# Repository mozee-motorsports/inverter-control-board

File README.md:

# mp7_ied (isolation-expansion-device)

Isolated CAN-addressable analog throttle for Sevcon.

- firmware in `src/`
  - to build: install Raspberry Pi Pico extension in vscode, open folder, click compile on bottom bar. 
- kicad project in `pcb/`

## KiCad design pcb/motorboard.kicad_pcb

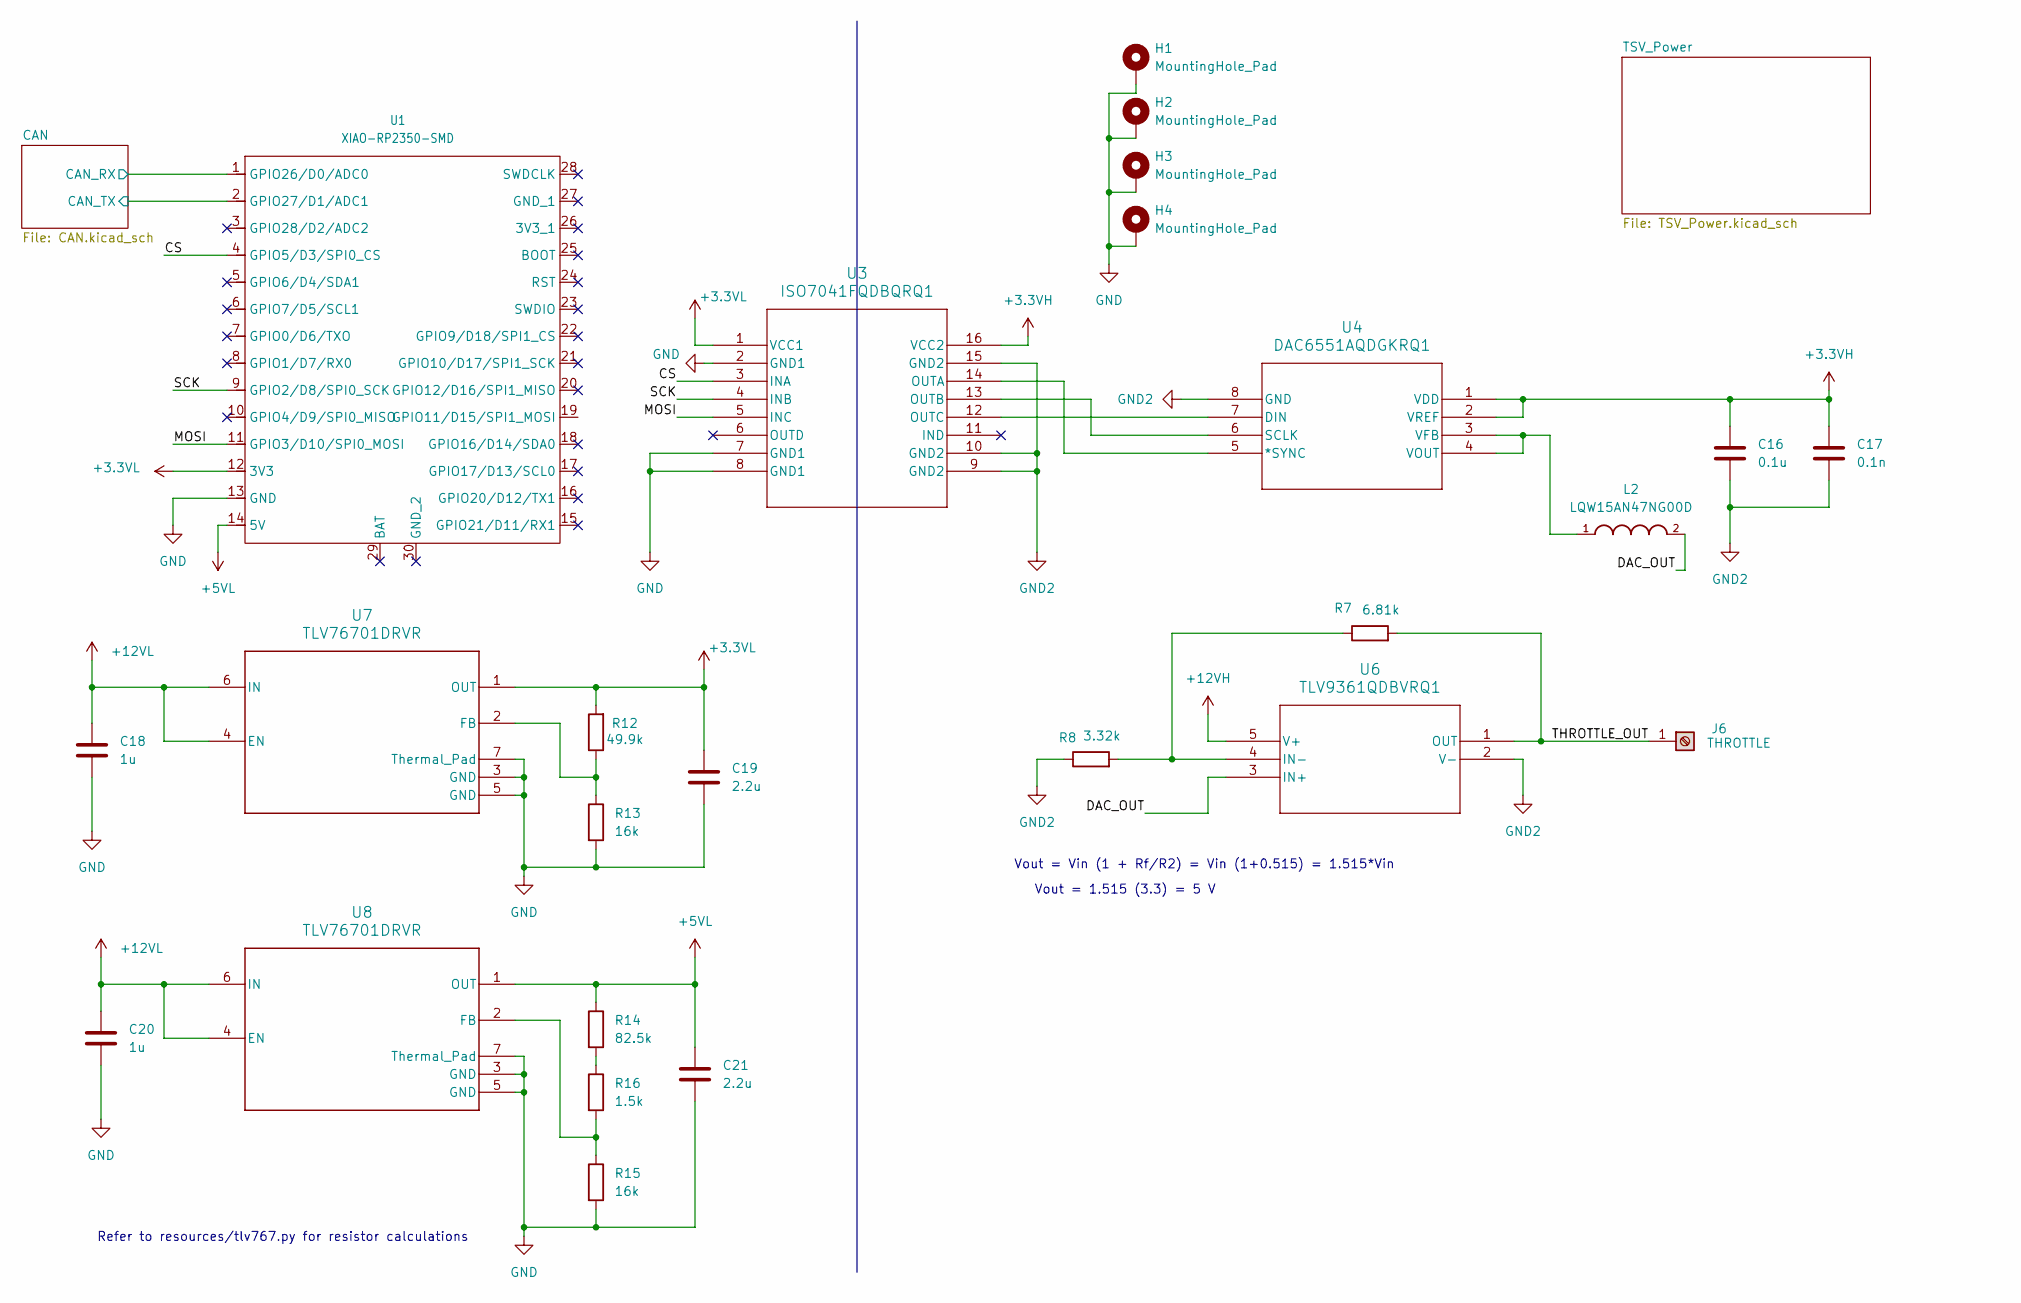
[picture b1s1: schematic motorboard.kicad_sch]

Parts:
C16: 0.1u; C_0603_1608Metric
C17: 0.1n; C_0603_1608Metric
C18, C20: 1u; C_0603_1608Metric
C19, C21: 2.2u; C_0603_1608Metric
H1, H2, H3, H4: MountingHole_Pad; MountingHole_2.2mm_M2
J6: THROTTLE; Wuerth_REDCUBE-THR_WP-THRBU_74650074_THR
L2: LQW15AN47NG00D; INDC1005X60N
R7: 6.81k; R_0603_1608Metric
R8: 3.32k; R_0603_1608Metric
R12: 49.9k; R_0603_1608Metric
R13, R15: 16k; R_0603_1608Metric
R14: 82.5k; R_0603_1608Metric
R16: 1.5k; R_0603_1608Metric
U1: XIAO-RP2350-SMD
U3: ISO7041FQDBQRQ1; SSOP16_DBQ_TEX
U4: DAC6551AQDGKRQ1; DGK8_TEX
U6: TLV9361QDBVRQ1; SOT23_DBV_TEX
U7, U8: TLV76701DRVR; DRV0006A-IPC_A

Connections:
+3.3VH: C16.1, C17.1, U3.16 (VCC2), U4.1 (VDD), U4.2 (VREF); also elsewhere on the board
+3.3VL: C19.1, R12.2, U1.12 (3V3), U3.1 (VCC1), U7.1 (OUT); also elsewhere on the board
+5VL: C21.1, R14.1, U1.14 (5V), U8.1 (OUT); also elsewhere on the board
+12VH: U6.5 (V+); also elsewhere on the board
+12VL: C18.1, C20.1, U7.4 (EN), U7.6 (IN), U8.4 (EN), U8.6 (IN); also elsewhere on the board
/CAN/CAN_RX: U1.1 (GPIO26/D0/ADC0); also elsewhere on the board
/CAN/CAN_TX: U1.2 (GPIO27/D1/ADC1); also elsewhere on the board
/CS: U1.4 (GPIO5/D3/SPI0_CS), U3.3 (INA)
/DAC_OUT: L2.2, U6.3 (IN+)
/MOSI: U1.11 (GPIO3/D10/SPI0_MOSI), U3.5 (INC)
/SCK: U1.9 (GPIO2/D8/SPI0_SCK), U3.4 (INB)
/THROTTLE_OUT: J6.1, R7.2, U6.1 (OUT)
GND: C18.2, C19.2, C20.2, C21.2, H1.1, H2.1, H3.1, H4.1, R13.2, R15.2, U1.13 (GND), U3.2 (GND1), U3.7 (GND1), U3.8 (GND1), U7.3 (GND), U7.5 (GND), U7.7 (Thermal_Pad), U8.3 (GND), U8.5 (GND), U8.7 (Thermal_Pad); also elsewhere on the board
GND2: C16.2, C17.2, R8.1, U3.9 (GND2), U3.10 (GND2), U3.15 (GND2), U4.8 (GND), U6.2 (V-); also elsewhere on the board
unnamed: R14.2, R16.1
unnamed: U3.14 (OUTA), U4.5 (*SYNC)
unnamed: U3.13 (OUTB), U4.6 (SCLK)
unnamed: U3.12 (OUTC), U4.7 (DIN)
unnamed: L2.1, U4.3 (VFB), U4.4 (VOUT)
unnamed: R7.1, R8.2, U6.4 (IN-)
unnamed: R12.1, R13.1, U7.2 (FB)
unnamed: R15.1, R16.2, U8.2 (FB)

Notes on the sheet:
Vout = 1.515 (3.3) = 5 V
Refer to resources/tlv767.py for resistor calculations
Vout = Vin (1 + Rf/R2) = Vin (1+0.515) = 1.515*Vin

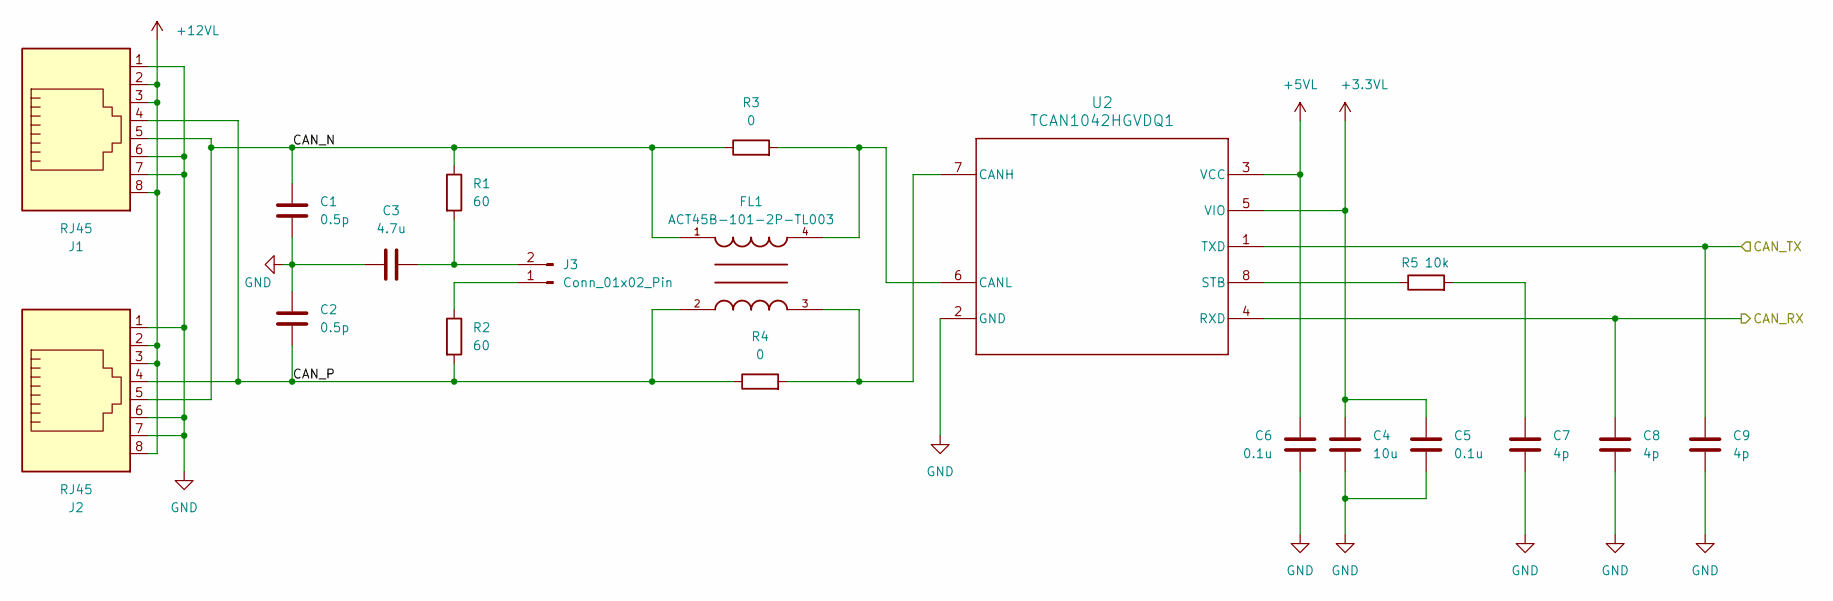
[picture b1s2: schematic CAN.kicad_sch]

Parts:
C1, C2: 0.5p; C_0402_1005Metric
C3: 4.7u; C_0805_2012Metric
C4: 10u; C_0805_2012Metric
C5, C6: 0.1u; C_0603_1608Metric
C7, C8, C9: 4p; C_0603_1608Metric
FL1: ACT45B-101-2P-TL003; FIL_ACT45B-101-2P-TL003; PARTREV 20200405
J1, J2: RJ45; RJ45_Amphenol_54602-x08_Horizontal
J3: Conn_01x02_Pin; PinHeader_1x02_P2.54mm_Vertical
R1, R2: 60; R_0603_1608Metric
R3, R4: 0; R_0603_1608Metric
R5: 10k; R_0603_1608Metric
U2: TCAN1042HGVDQ1; D0008A_L

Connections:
+3.3VL: C4.1, C5.1, U2.5 (VIO); also elsewhere on the board
+5VL: C6.2, U2.3 (VCC); also elsewhere on the board
+12VL: J1.2, J1.3, J1.8, J2.2, J2.3, J2.8; also elsewhere on the board
/CAN/CAN_N: C1.2, FL1.1, J1.5, J2.5, R1.1, R3.1
/CAN/CAN_P: C2.1, FL1.2, J1.4, J2.4, R2.2, R4.1
/CAN/CAN_RX: C8.1, U2.4 (RXD); also elsewhere on the board
/CAN/CAN_TX: C9.1, U2.1 (TXD); also elsewhere on the board
GND: C1.1, C2.2, C3.2, C4.2, C5.2, C6.1, C7.2, C8.2, C9.2, J1.1, J1.6, J1.7, J2.1, J2.6, J2.7, U2.2 (GND); also elsewhere on the board
unnamed: C7.1, R5.2
unnamed: J3.1, R2.1
unnamed: C3.1, J3.2, R1.2
unnamed: FL1.3, R4.2, U2.7 (CANH)
unnamed: FL1.4, R3.2, U2.6 (CANL)
unnamed: R5.1, U2.8 (STB)

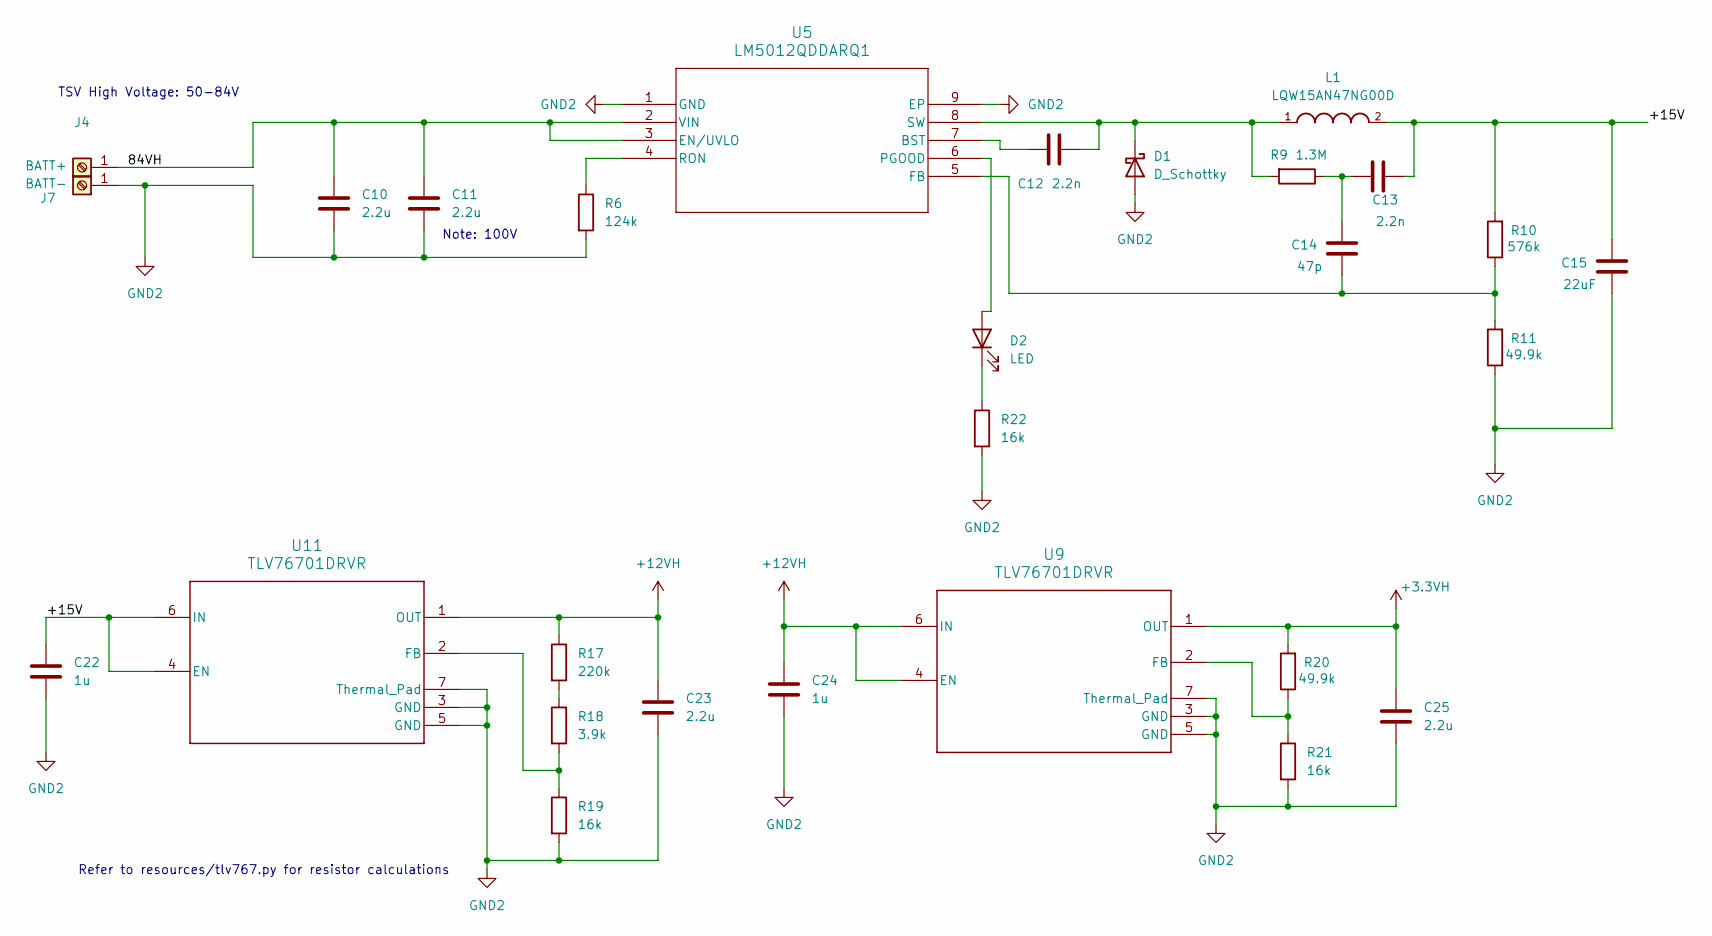
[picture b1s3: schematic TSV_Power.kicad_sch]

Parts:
C10, C11: 2.2u; C_1210_3225Metric_Pad1.33x2.70mm_HandSolder
C12, C13: 2.2n; C_0805_2012Metric
C14: 47p; C_0805_2012Metric
C15: 22uF; C_1210_3225Metric
C22, C24: 1u; C_0603_1608Metric
C23, C25: 2.2u; C_0603_1608Metric
D1: D_Schottky; D_DO-201AD_P15.24mm_Horizontal
D2: LED; LED_0805_2012Metric
J4: BATT+; Wuerth_REDCUBE-THR_WP-THRBU_74650074_THR
J7: BATT-; Wuerth_REDCUBE-THR_WP-THRBU_74650074_THR
L1: LQW15AN47NG00D; INDC1005X60N
R6: 124k; R_0402_1005Metric
R9: 1.3M; R_0402_1005Metric_Pad0.72x0.64mm_HandSolder
R10: 576k; R_0603_1608Metric
R11, R20: 49.9k; R_0603_1608Metric
R17: 220k; R_0603_1608Metric
R18: 3.9k; R_0603_1608Metric
R19, R21, R22: 16k; R_0603_1608Metric
U5: LM5012QDDARQ1; SO-8-DDA_TEX
U9, U11: TLV76701DRVR; DRV0006A-IPC_A

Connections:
+3.3VH: C25.1, R20.2, U9.1 (OUT); also elsewhere on the board
+12VH: C23.1, C24.1, R17.1, U9.4 (EN), U9.6 (IN), U11.1 (OUT); also elsewhere on the board
/TSV_Power/84VH: C10.1, C11.1, J4.1, U5.2 (VIN), U5.3 (EN/UVLO); also elsewhere on the board
/TSV_Power/+15V: C13.2, C15.1, C22.1, L1.2, R10.2, U11.4 (EN), U11.6 (IN)
GND2: C10.2, C11.2, C15.2, C22.2, C23.2, C24.2, C25.2, D1.2 (A), J7.1, R6.2, R11.1, R19.2, R21.2, R22.2, U5.1 (GND), U5.9 (EP), U9.3 (GND), U9.5 (GND), U9.7 (Thermal_Pad), U11.3 (GND), U11.5 (GND), U11.7 (Thermal_Pad); also elsewhere on the board
unnamed: C13.1, C14.1, R9.1
unnamed: C12.2, D1.1 (K), L1.1, R9.2, U5.8 (SW)
unnamed: D2.2 (A), U5.6 (PGOOD)
unnamed: D2.1 (K), R22.1
unnamed: R17.2, R18.1
unnamed: C12.1, U5.7 (BST)
unnamed: C14.2, R10.1, R11.2, U5.5 (FB)
unnamed: R6.1, U5.4 (RON)
unnamed: R20.1, R21.1, U9.2 (FB)
unnamed: R18.2, R19.1, U11.2 (FB)

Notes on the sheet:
Refer to resources/tlv767.py for resistor calculations
Note: 100V
TSV High Voltage: 50-84V

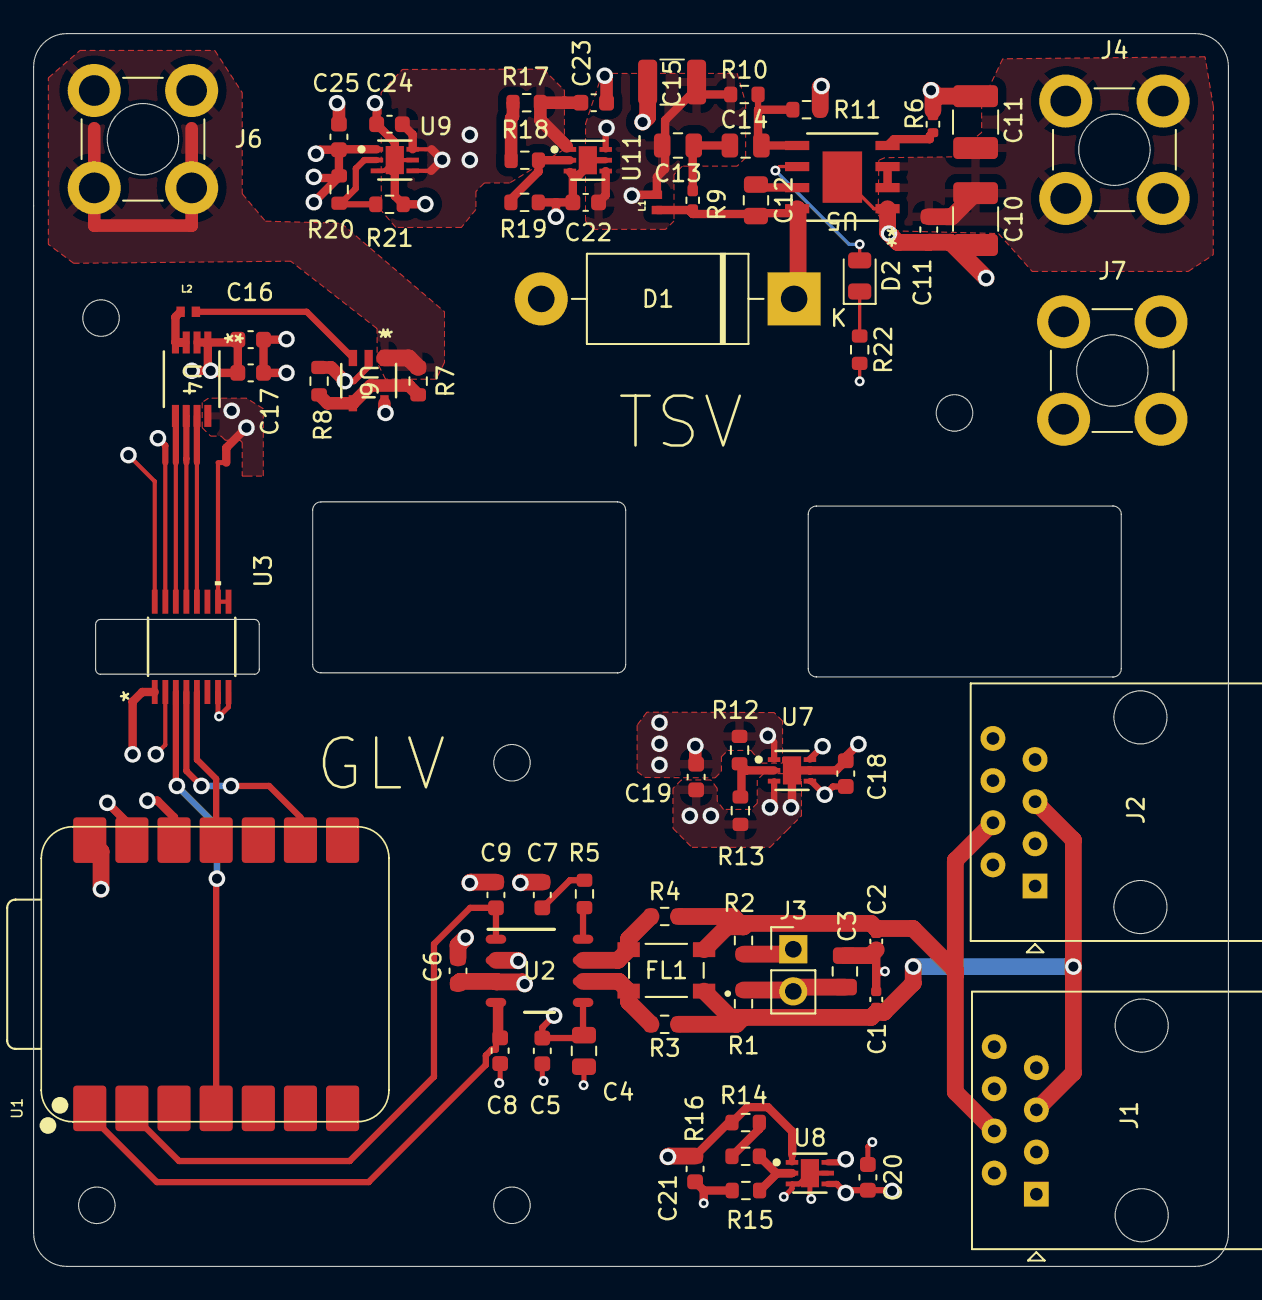
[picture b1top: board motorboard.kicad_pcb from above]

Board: 4 copper layers, 72.0 x 74.3 mm, 74 parts (0 on the bottom side), 42 nets.

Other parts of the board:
C11#2: 2.2u; C_1210_3225Metric_Pad1.33x2.70mm_HandSolder
H3#2: MountingHole_Pad; MountingHole_2.2mm_M2

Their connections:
/TSV_Power/84VH: C11#2.1; also elsewhere on the board
GND2: C11#2.2; also elsewhere on the board

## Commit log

2025-02-28 initial
2025-02-28 save
2025-03-03 switch isolator for SPI, output stage (DAC, op amp)
2025-03-03 Schematic done, pending review
2025-03-04 Initial layout, all resistors/caps are 0602
2025-03-11 layout finished, silkscreen finished, BOM finished
2025-04-10 pcb that we ordered with
2025-04-10 test projects
2025-04-21 basic firmware, CAN consumption -> DAC only, no frame format
2025-04-21 CAN frame format
2025-04-21 modularize
